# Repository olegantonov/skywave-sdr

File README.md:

# SkyWave SDR

**Transceptor modular open source com ESP32-S3, OLED, PTT e acesso USB.**
Projeto de Daniel Marques, com prioridade para baixo custo e montagem incremental.

A revisão **D1** inclui circuitos, oito projetos KiCad, seleção de componentes,
simulações, modelos STEP e gabinete paramétrico em STL. É um protótipo de engenharia:
nenhuma placa foi fabricada ou ensaiada fisicamente. O firmware disponível ainda é
de interface e mantém a transmissão bloqueada, pois drivers RF/DSP estão pendentes.

## Abrir o projeto

- **[Circuito, PCB, BOM, ligações e testes D1](hardware/d1/README.md)**
- [Esquemas e placas KiCad editáveis](hardware/d1/ecad)
- [PDFs dos esquemas e curvas dos filtros](hardware/d1/plots)
- [Montagem 3D STEP](hardware/d1/cad/skywave_d1_assembly.step)
- [Base STL](hardware/d1/cad/enclosure_base.stl) e [tampa STL](hardware/d1/cad/enclosure_lid.stl)
- [Relatórios ERC/DRC](hardware/d1/reports/checks.json), [simulações](hardware/d1/reports/simulation.json)
  e [geometria](hardware/d1/reports/mechanical.json)

## Arquitetura

| Bloco | Implementação D1 |
|---|---|
| Controle | ESP32-S3-WROOM-1-N8, OLED SH1106/SSD1306, botões e PTT físico |
| Acesso | USB-C de dados/console, GPIO19/20; alimentação externa regulada de 5 V |
| HF 40/20/15/10 m | Codec TLV320AIC3204, Si5351A, quadratura, misturadores I/Q RX/TX e filtros intercambiáveis |
| VHF 2 m | DRA818V, FM analógica controlada por UART, fonte e filtro próprios |
| UHF 70 cm | DRA818U, FM analógica controlada por UART, fonte e filtro próprios |
| Áudio | Eletreto externo, comutação analógica, LM386 e saída para falante de 8 Ω |
| Gabinete | Montagem de bancada 164 × 120 × 74 mm; miniaturização posterior |

**A versão econômica é híbrida.** HF tem arquitetura SDR I/Q; DRA818 VHF/UHF não
expõem amostras I/Q e não são SDR aberto. A expansão I/Q VHF/UHF continua planejada.
HF D1 é um excitador de baixo nível, sem PA. Nos DRA, H/L aterrado seleciona potência
nominal de 0,5 W; potência, sensibilidade e emissões não foram medidas neste projeto.

```mermaid
flowchart LR
    UI[OLED + botoes + PTT] <--> MCU[ESP32-S3]
    USB[USB-C dados] <--> MCU
    MCU <-->|I2S| CODEC[TLV320AIC3204]
    MCU -->|I2C| LO[Si5351 + quadratura]
    LO --> HF[Misturadores HF RX/TX]
    CODEC <--> HF
    HF <--> LPF[Rele T/R + cartucho LC]
    LPF <--> A[SMA HF]
    MIC[Microfone / falante] <--> AUDIO[Comutacao de audio]
    AUDIO <--> CODEC
    MCU -->|UART| V[DRA818V + filtro]
    MCU -->|UART| U[DRA818U + filtro]
    AUDIO <--> V
    AUDIO <--> U
    PWR[5 V externo] --> MCU
    PWR --> BUCK[Fontes RF 4 V]
    BUCK --> V
    BUCK --> U
```

O planejamento aproveitou a separação entre hardware, firmware, interface e energia
estudada no SkySentinel. Este repositório é independente: não publica código,
esquemas, memórias ou dados privados daquele projeto.

## Firmware

C++17 com Arduino/PlatformIO. Duas variantes OLED, sintonia por botões, console,
watchdog e lógica de PTT com timeout de 30 s. A frequência exibida é uma prévia;
a tela informa `PREVIEW - NO RF` e PTT resulta em `TX BLOQUEADO`.

Na D1, TX_ARM e PD dos módulos permanecem em zero, resets de codec/quadratura
ativos e seletor de módulo na posição desabilitada. Ainda faltam drivers do codec,
LO e DRA, DSP SSB, AGC, calibração I/Q e sequência de T/R com tempos medidos.

```bash
python3 -m venv .venv
. .venv/bin/activate
pip install platformio==6.1.18
pio run -e esp32s3_oled -e esp32s3_ssd1306
mkdir -p build
g++ -std=c++17 -Wall -Wextra -Werror -pedantic -fsanitize=undefined \
  -Ifirmware/include tests/radio_test.cpp -o build/radio_test
./build/radio_test
python3 tests/hardware_test.py
```

Console: `?` consulta estado, `+`/`-` sintonizam, `b` troca banda. Não existe
comando de transmissão remota. GPIOs estão em [`pins.h`](firmware/include/pins.h);
as ligações completas estão no [guia D1](hardware/d1/README.md).

## Validação e próximos passos

Os relatórios registram o que passou e os achados pendentes. Simulação ngspice,
ERC/DRC, testes de software e verificação de sólidos 3D não substituem ensaios de
bancada. PCB, stackup/impedâncias, dissipação, encaixes e acessórios precisam de
revisão antes da montagem; consultar o estado de fabricação nos relatórios D1.

A estratégia de custo é montar controle e apenas um módulo inicialmente. O preço
final ainda não foi cotado. A BOM identifica partes principais e especificações
de passivos; não é uma lista de compra fechada com frete e montagem.

Próximas etapas: validar fontes e interface, implementar HF RX, ensaiar HF TX em
carga de 50 Ω, integrar VHF/UHF FM e então desenvolver bateria e miniaturização.
Os perfis de frequência não são autorização para transmissão nem plano regulatório.

## Contribuição e licença

Contribuições por issues e PRs, com Conventional Commits e evidências de testes.
Arquivos originais: [MIT](LICENSE). Footprints KiCad mantêm sua
[licença própria](hardware/d1/ecad/SkyWave.pretty/LICENSE.md). Dependências,
datasheets e módulos comerciais mantêm as respectivas licenças.

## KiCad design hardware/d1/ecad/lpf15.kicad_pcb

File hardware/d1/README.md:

# SkyWave D1 — circuito, PCB e gabinete

Protótipo de engenharia de Daniel Marques. Os arquivos são editáveis; esta revisão
não é uma liberação para fabricação em série. Ensaios RF, térmicos e de montagem
física não foram realizados. O firmware continua sem backend RF e mantém TX bloqueado.

## Arquivos

- [Esquemas e placas KiCad](ecad): oito projetos, biblioteca local e roteamento.
- [BOM por referência](bom.csv) e [circuito com todas as conexões](design.json).
- [Fontes dos fabricantes](sources.json), com hashes quando o PDF foi obtido.
- [Montagem STEP](cad/skywave_d1_assembly.step), placas individuais, base e tampa em STEP/STL.
- [Simulações](reports/simulation.json), [ERC/DRC completos](reports/checks.json)
  e [verificação mecânica](reports/mechanical.json).
- [Curvas dos filtros](plots/filter_response.pdf) e [netlists ngspice](simulation).
- [Gerber e Excellon por placa](fabrication_prototype), exportados com o bloqueio de verificações ativo.

## Resultado das verificações — 12/10/2026

| Verificação executada | Resultado |
|---|---|
| KiCad ERC/DRC, 8 placas | Zero erros, zero avisos e zero conexões pendentes |
| 915 pads comparados ao circuito | Redes, números de pino, valores e posições conferem |
| 6 filtros em ngspice | Conferem com cálculo independente por matrizes ABCD |
| 1.800 casos de tolerância LC | Atendem às metas do modelo com Q=35; não são medições |
| Modelos STEP e interseções | Sólidos válidos, sem colisões entre placas ou contra base/tampa |
| Firmware | Duas variantes compiladas; testes nativos de controle passaram com UBSan |
| Contratos de artefatos | 4 testes Python passaram |

Hashes das placas e esquemas constam dos relatórios. Os testes digitais de PTT e
quadratura são verificações lógicas; não incluem atrasos reais dos componentes.
O resultado não valida o desempenho do rádio completo nem substitui bancada.

## Placas e componentes

| Placa | Dimensões | Circuito |
|---|---|---|
| Controle | 120 × 100 mm, 2 camadas | ESP32-S3-WROOM-1-N8, OLED I²C externo, USB4105, USBLC6-2SC6, LM1117, lógica de PTT, CD74HCT4052, LM386 |
| HF | 120 × 100 mm, 4 camadas | TLV320AIC3204, TLV75518, Si5351A, 74LVC74A, dois SN74CBT3253, dois TLV9064, relé G6K |
| VHF | 60 × 70 mm, 4 camadas | DRA818V, TPS62160, buffer UART e filtro de saída |
| UHF | 60 × 70 mm, 4 camadas | DRA818U, TPS62160, buffer UART e filtro de saída |
| Filtros HF | 48 × 24 mm cada, 4 camadas | Cartuchos LC de sete polos para 40/20/15/10 m, identificação resistiva |

HF usa conversão I/Q em recepção e transmissão. É um **excitador de baixo nível**,
sem PA. A potência e a supressão de imagem/portadora ainda precisam ser medidas.
Os DRA818 são módulos de voz FM controlados por UART; **não oferecem SDR I/Q aberto**.
H/L aterrado seleciona o modo nominal de 0,5 W, que não foi medido neste projeto.
Somente um módulo pode receber habilitação de transmissão por vez.

A BOM contém MPNs dos circuitos principais e famílias/especificações de parte dos
passivos. Ainda requer fechamento dos códigos de compra, preços e equivalentes.
Os indutores HF são Coilcraft 0805CS; a simulação com Q=35 não garante o Q real
desses componentes em cada frequência. Confirmar perdas e autorressonância na bancada.
O relatório também calcula a sensibilidade a Q=10/20/35/50. O indutor de potência
TDK VLS3015ET-2R2M está marcado NRND pelo fabricante; para a próxima revisão,
selecionar uma alternativa ativa e conferir novamente footprint, corrente e perdas.

## Energia, portas e conexões

**Entrada: 5 V regulados, fonte de pelo menos 2 A em J3 da placa de controle.**
J3.1 = +5 V; J3.2 = GND. Não há proteção contra inversão, carregador, bateria ou
power-path. USB-C nesta revisão leva **dados e referência VBUS para ESD**; não
alimenta o sistema. Nunca ligar célula de lítio diretamente a J3.

O LM1117 fornece 3,3 V. A dissipação estimada a 400 mA é 0,68 W; temperatura precisa
ser medida. Cada DRA tem buck de aproximadamente 4,02 V, nominalmente até 1 A.
O cálculo de consumo está em `reports/simulation.json`; não é autonomia medida.

| Interface do controle | Ligação |
|---|---|
| J1 PTT externo | 1 = PTT ativo em zero; 2 = GND; contato normalmente aberto |
| J2 OLED | 1 GND, 2 +3V3, 3 SCL, 4 SDA; verificar ordem no módulo comprado |
| J3 energia | 1 +5V, 2 GND |
| J4 USB-C | Console e programação; GPIO19 D− / GPIO20 D+ |
| J5 HF, 2×10 | Cabo pino a pino para J1 HF; máximo curto de bancada, ainda sem SI medida |
| J6 VHF / J7 UHF, 2×5 | Cabo pino a pino para J1 do módulo correspondente |
| J8 microfone | 1 sinal polarizado, 2 GND; cápsula eletreto externa |
| J9 alto-falante | 1 áudio desacoplado, 2 GND; 8 Ω |

As tabelas completas de pinos e redes estão em `design.json` e nos esquemas.
Orientar os cabos pelo pino 1, não pela posição visual dos conectores.
Os cartuchos HF usam cabo curto 2×3 para J2 HF; instalar somente um cartucho por vez.
Usam IDs de 1 kΩ, 2,2 kΩ, 4,7 kΩ e 10 kΩ. A leitura/validação pelo firmware está pendente.

PTT físico e GPIO38/TX_ARM passam por lógica AND/NAND e decodificador SN74HC139.
GPIO39/40 selecionam HF/VHF/UHF; valor 3 desabilita todos. GPIO41/42 controlam PD
dos DRA. Pull-down em TX_ARM mantém TX desabilitado durante reset; o firmware
mantém ARM, PD, reset do codec e reset da quadratura em zero nesta revisão.
Essa lógica não mede filtro, potência, VSWR ou temperatura.

## Limites do layout e da mecânica

O roteamento é um ponto de partida para revisão elétrica. ERC/DRC verificam regras
geométricas e conectividade; não demonstram integridade de sinal, impedância RF,
estabilidade do buck, USB ou desempenho do codec. Conferir os relatórios completos,
incluindo ligações pendentes e avisos, antes de qualquer pedido de placas.
O stackup precisa ser acordado com o fabricante; linhas RF de 50 Ω, par USB de
90 Ω, retorno de terra e desacoplamentos exigem revisão específica.

O gabinete de bancada mede **164 × 120 × 74 mm**, com paredes de 2,5 mm. É uma
primeira montagem modular, maior que o formato portátil final. As placas recebem
suportes internos; a tampa tem janela de display, três botões e ventilação.
Há acesso ao USB e passagens para PTT, energia e três SMA de painel com pigtails.
Conectores, speaker, microfone e cabos de painel ainda não têm montagem física validada.

Os STEP dos componentes usam envelopes derivados de footprints, não modelos
certificados de fabricante. A bandeja OLED assume módulo de 35,6 × 33,7 mm;
medir o módulo escolhido e ajustar `mechanical.py` antes de imprimir. Folgas de
impressão, curso dos botões, parafusos e volume de cabos precisam de ensaio.

## Reprodução

Os scripts originais estão em [`tools/hardware`](../../tools/hardware).
Dependências utilizadas: KiCad 7 para `pcbnew`, KiCad CLI 10.0.7 para ERC/DRC,
CadQuery 2.8.0, NumPy, Matplotlib, sexpdata, ngspice 42 e Freerouting 2.1.0/Java 21.
Os caminhos de ferramentas podem ser configurados por variáveis de ambiente;
os defaults refletem a estação de desenvolvimento.

1. `python tools/hardware/acquire.py`: obter referências públicas.
2. `python tools/hardware/ecad.py`: gerar esquemas e placas iniciais. **Sobrescreve roteamento.**
3. `python tools/hardware/route.py prepare`: preparar DSNs; executar Freerouting
   em cada DSN e salvar SES com o mesmo nome.
   Para HF, executar `hf_escape.py` antes do roteador: ele prepara escapes alternados
   dos encapsulamentos finos com vias de 0,5/0,25 mm.
4. `python tools/hardware/route.py finish`: importar trilhas/vias e preencher planos.
   Aplicar `refine.py` em HF/VHF/UHF para acabamento dos SMA, PTT e costura de terra.
5. `python tools/hardware/check.py`: executar ERC/DRC reais, sem apagar achados.
   `verify_pcb.py` confere os pads dos arquivos salvos contra o circuito.
   `cleanup.py <placas>` remove apenas stubs apontados pelo DRC; repetir a verificação
   após essa edição. Mudanças nas placas invalidam os hashes anteriores.
6. `python tools/hardware/analyze.py`: executar ngspice e tolerâncias dos filtros.
7. `python tools/hardware/mechanical.py` e `render.py`: gerar STEP/STL e imagem.

`export.py --manufacturing` só exporta Gerber/Excellon quando ERC/conectividade/DRC
passaram e o hash da placa confere com o relatório. A exportação continua marcada
como protótipo. Há uma regra explícita para os pads SMA de montagem na borda;
as demais regiões mantêm afastamento de 0,5 mm da borda. Vias em pads exigem
avaliação de montagem; esta revisão prioriza soldagem e inspeção de bancada.

Não foram fabricadas, energizadas ou testadas placas físicas durante esta revisão.
Próximos ensaios: fontes sem RF, OLED/USB/PTT, clock e codec, RX, depois TX em carga
de 50 Ω com analisador de espectro. Firmware DSP, drivers e sequência de T/R pendentes.

## Licenças

Arquivos originais: [MIT](../../LICENSE). Footprints copiados da biblioteca KiCad 7
mantêm [CC-BY-SA 4.0 com exceção KiCad](ecad/SkyWave.pretty/LICENSE.md); origem:
https://github.com/KiCad/kicad-footprints. A biblioteca foi copiada para tornar os
projetos independentes da versão instalada. DRA818 e VLS3015ET são footprints
originais deste projeto. Datasheets não são redistribuídos sob MIT.
O footprint MSOP-10 foi adaptado para herdar a regra de espaçamento de 0,15 mm
do projeto, em vez de impor o override de 0,20 mm da biblioteca original.

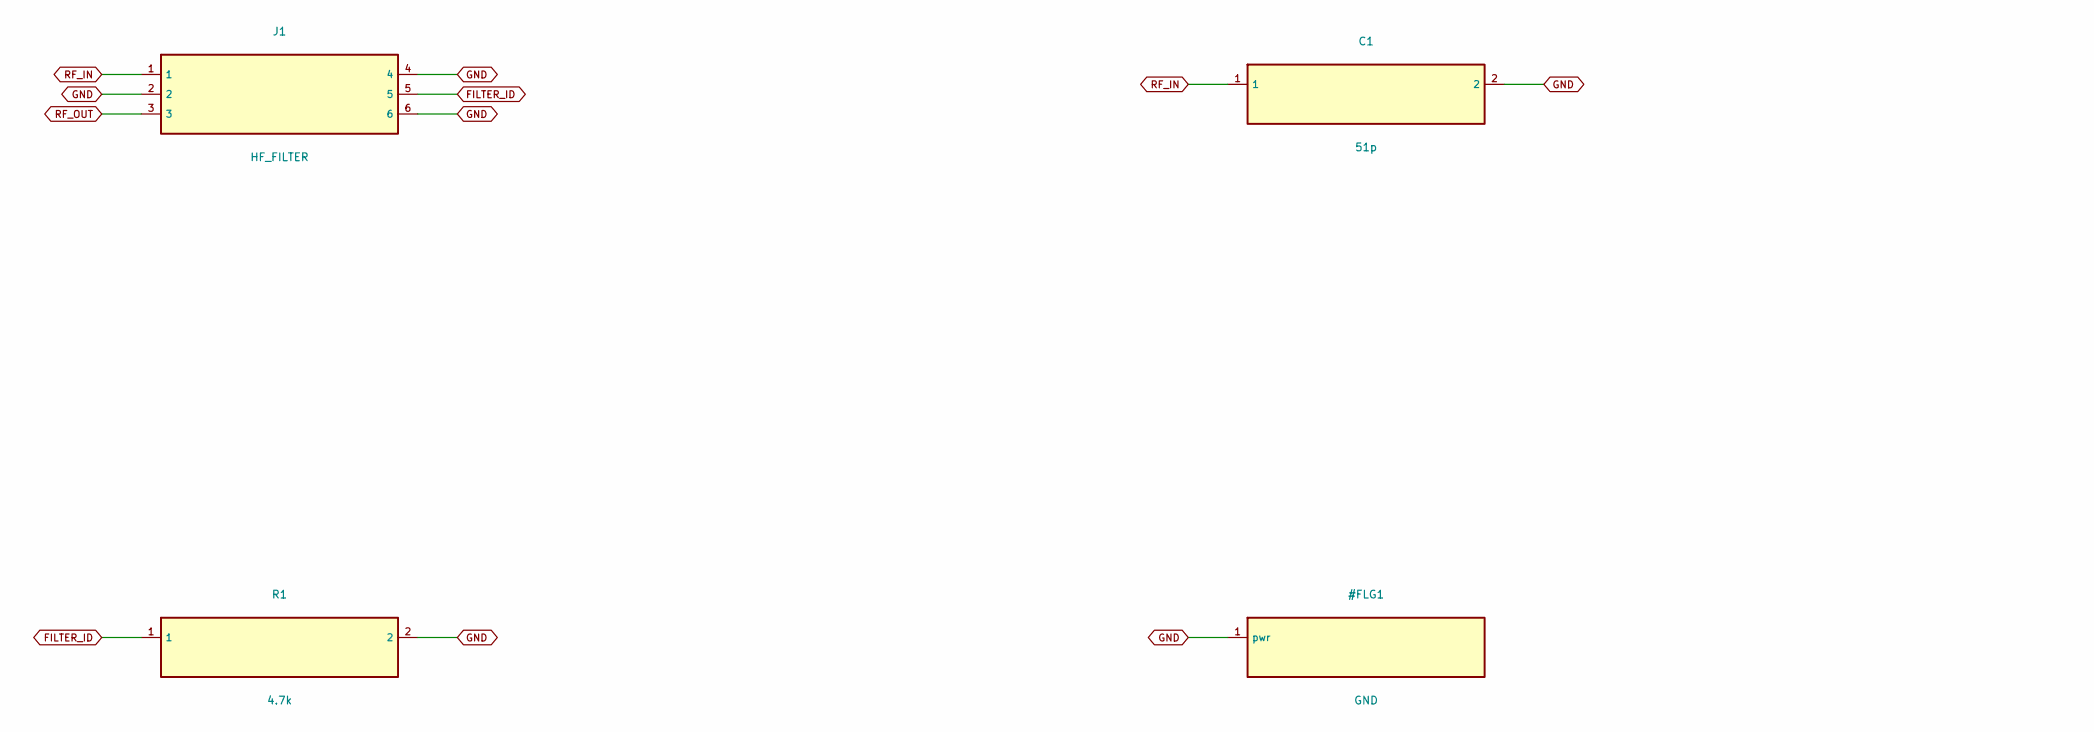
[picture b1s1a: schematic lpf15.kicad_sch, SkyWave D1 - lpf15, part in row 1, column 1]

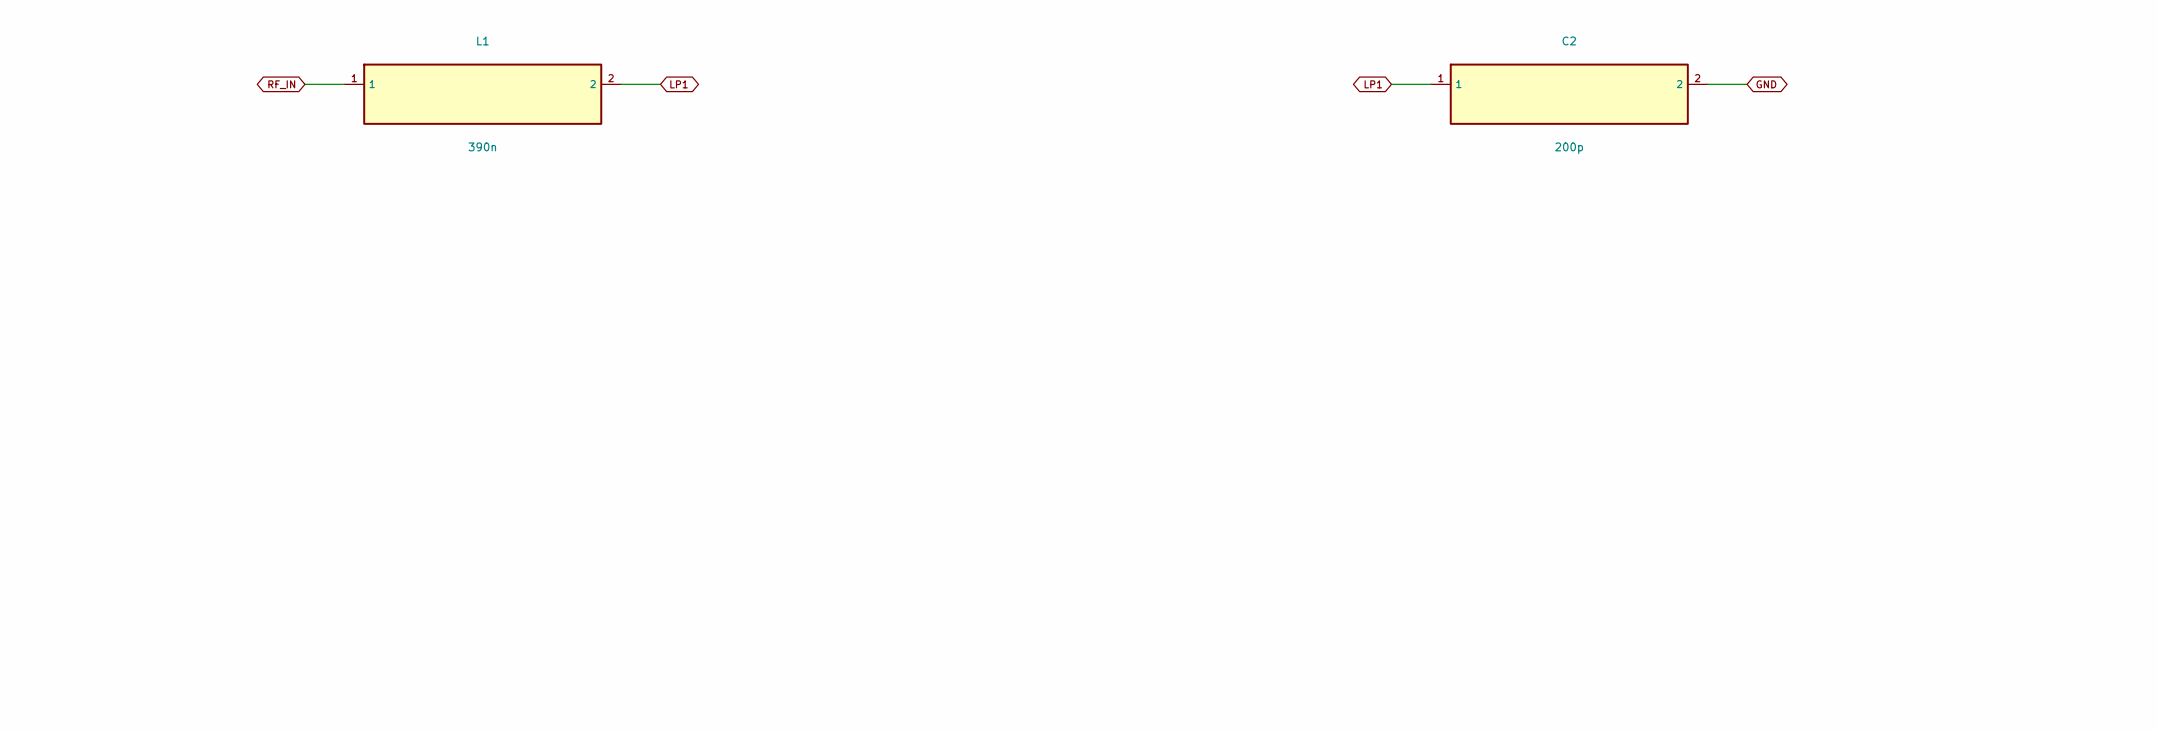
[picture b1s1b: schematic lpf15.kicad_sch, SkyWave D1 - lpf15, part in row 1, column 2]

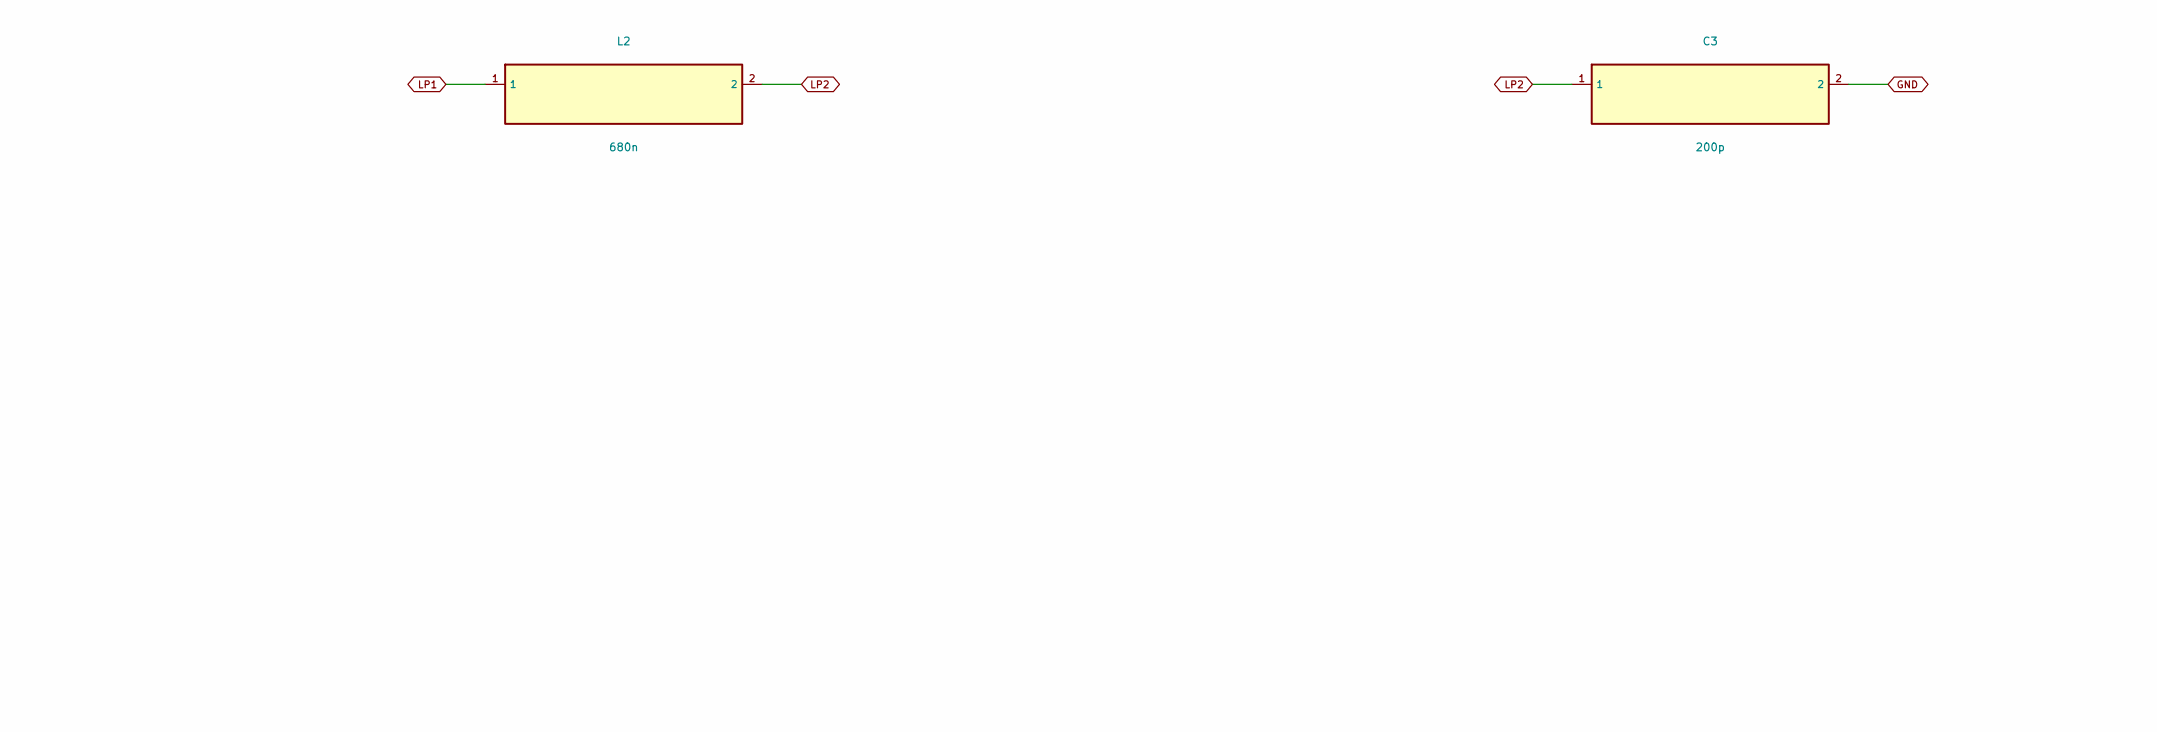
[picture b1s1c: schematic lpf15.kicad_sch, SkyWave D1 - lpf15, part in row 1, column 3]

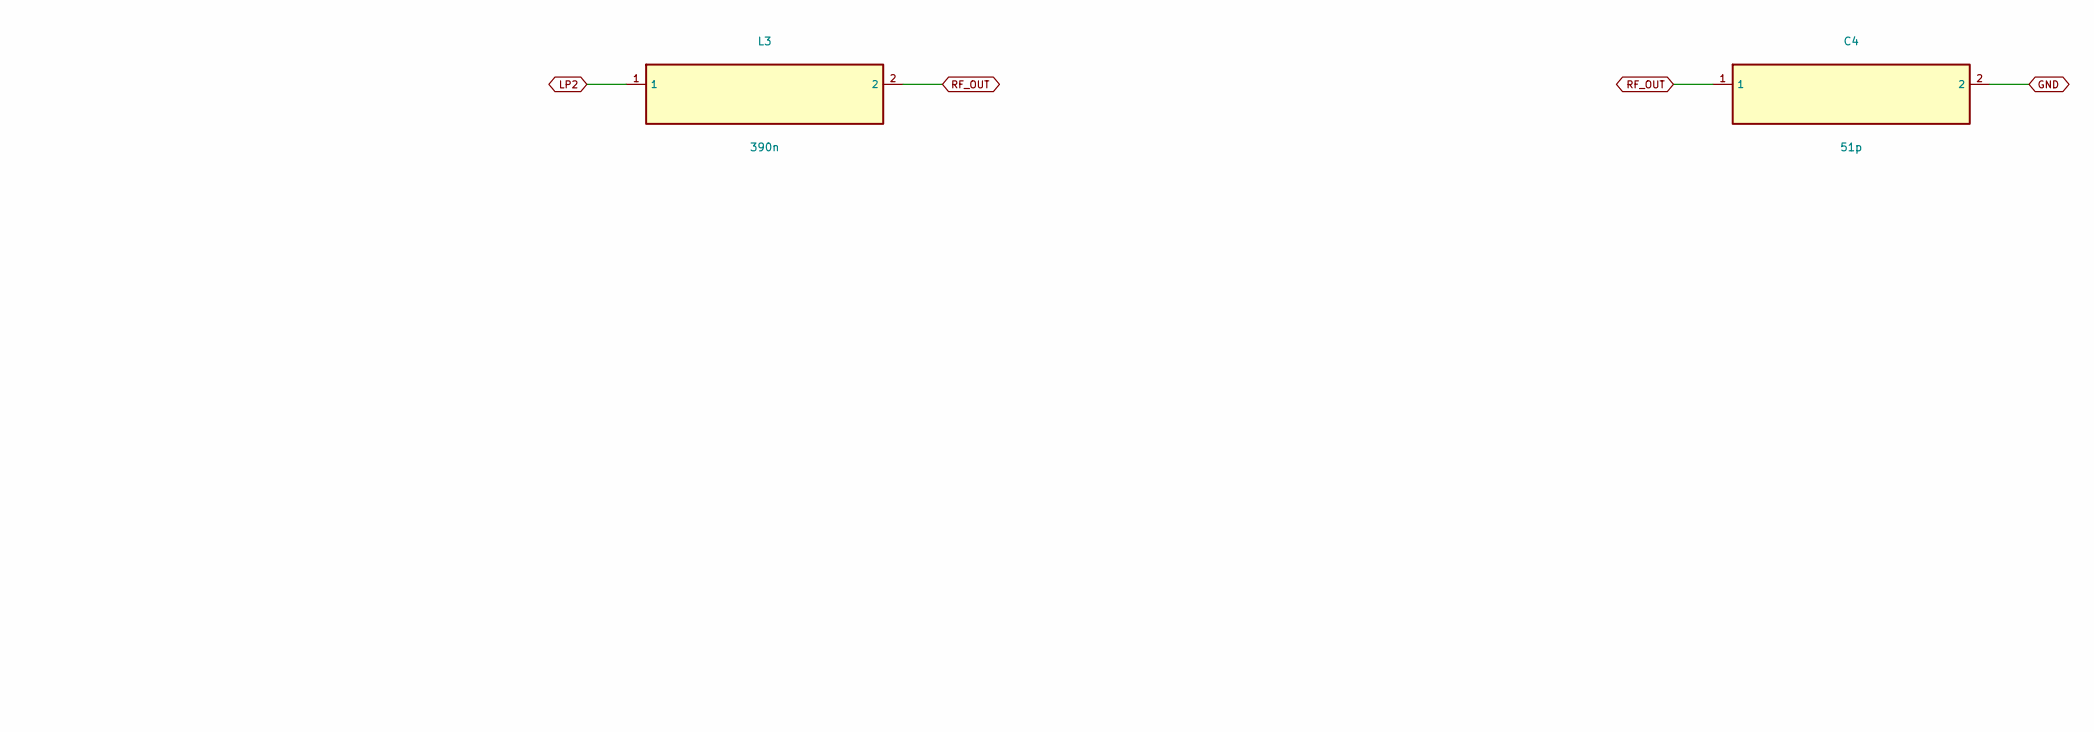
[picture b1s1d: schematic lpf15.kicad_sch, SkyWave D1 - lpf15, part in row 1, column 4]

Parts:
C1, C4: 51p; Capacitor_SMD_C_0603_1608Metric; MPN KEMET 0603 C0G 25V; 51p; 5% RF/10% deco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
C2, C3: 200p; Capacitor_SMD_C_0603_1608Metric; MPN KEMET 0603 C0G 25V; 200p; 5% RF/10% dec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
J1: HF_FILTER; Connector_PinHeader_2.54mm_PinHeader_2x03_P2.54mm_Vertical; MPN Samtec TSW-003-07-D-S
L1, L3: 390n; Inductor_SMD_L_0805_2012Metric; MPN 0805CS-391XJRC
L2: 680n; Inductor_SMD_L_0805_2012Metric; MPN 0805CS-681XJRC
R1: 4.7k; Resistor_SMD_R_0603_1608Metric; MPN CRCW0603 series; value=4.7k; 1%

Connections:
FILTER_ID: J1.5, R1.1
GND: C1.2, C2.2, C3.2, C4.2, J1.2, J1.4, J1.6, R1.2
LP1: C2.1, L1.2, L2.1
LP2: C3.1, L2.2, L3.1
RF_IN: C1.1, J1.1, L1.1
RF_OUT: C4.1, J1.3, L3.2

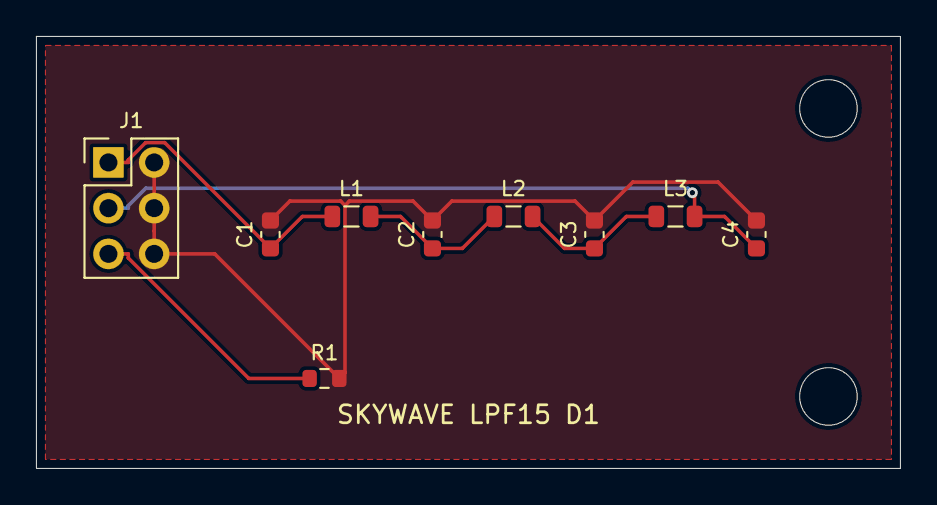
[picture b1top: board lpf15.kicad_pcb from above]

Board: 4 copper layers, 48.0 x 24.0 mm, 11 parts (0 on the bottom side), 6 nets.

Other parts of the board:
H1, H2: MountingHole_3.2mm_M3

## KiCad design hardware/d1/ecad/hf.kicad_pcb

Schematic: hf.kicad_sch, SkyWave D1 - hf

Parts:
C1, C2, C8, C9, C16, C20, C22, C25: 1u; Capacitor_SMD_C_0603_1608Metric; MPN KEMET 0603 X7R 25V; 1u; 5% RF/10% decou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
C3, C4, C5, C6, C10, C11, C21, C28, C29, C30, C35, C36: 100n; Capacitor_SMD_C_0603_1608Metric; MPN KEMET 0603 X7R 25V; 100n; 5% RF/10% dec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
C7, C12, C37, C38: 10u; Capacitor_SMD_C_0805_2012Metric; MPN KEMET 0805 X7R 25V; 10u; 5% RF/10% deco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
C13, C14, C17, C18: 100p; Capacitor_SMD_C_0603_1608Metric; MPN KEMET 0603 C0G 25V; 100p; 5% RF/10% dec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
C15, C19, C23, C24, C26, C27, C31, C32, C33, C34: 10n; Capacitor_SMD_C_0603_1608Metric; MPN KEMET 0603 C0G 25V; 10n; 5% RF/10% deco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
D1: 1N4148W; Diode_SMD_D_SOD-123; MPN 1N4148W
J1: CONTROL_INTERFACE; Connector_PinHeader_2.54mm_PinHeader_2x10_P2.54mm_Vertical; MPN Samtec TSW-010-07-D-S
J2: FILTER_CARTRIDGE; Connector_PinHeader_2.54mm_PinHeader_2x03_P2.54mm_Vertical; MPN Samtec TSW-003-07-D-S
J3: SMA 132289; Connector_Coaxial_SMA_Amphenol_132289_EdgeMount; MPN Amphenol 132289
K1: G6K-2F-Y-DC5; Relay_SMD_Relay_DPDT_Omron_G6K-2F-Y; MPN G6K-2F-Y-DC5
Q1: 2N7002; Package_TO_SOT_SMD_SOT-23; MPN 2N7002
R1, R3, R4, R5, R6, R7, R9, R12, R14, R18, R19, R23, R24: 10k; Resistor_SMD_R_0603_1608Metric; MPN CRCW0603 series; value=10k; 1%
R2: 33; Resistor_SMD_R_0603_1608Metric; MPN CRCW0603 series; value=33; 1%
R8, R10, R13, R15, R17, R22, R29: 100k; Resistor_SMD_R_0603_1608Metric; MPN CRCW0603 series; value=100k; 1%
R11, R16: 1k; Resistor_SMD_R_0603_1608Metric; MPN CRCW0603 series; value=1k; 1%
R20, R21, R25, R26: 100; Resistor_SMD_R_0603_1608Metric; MPN CRCW0603 series; value=100; 1%
R27, R28: 49.9; Resistor_SMD_R_0603_1608Metric; MPN CRCW0603 series; value=49.9; 1%
U1: TLV75518PDBVR; Package_TO_SOT_SMD_SOT-23-5; MPN TLV75518PDBVR
U2: TLV320AIC3204IRHBR; Package_DFN_QFN_Texas_RHB0032E_VQFN-32-1EP_5x5mm_P0.5mm_EP3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; MPN TLV320AIC3204IRHBR
U3: SI5351A-B-GT; Package_SO_MSOP-10_3x3mm_P0.5mm; MPN SI5351A-B-GT
U4: 74LVC74APW; Package_SO_TSSOP-14_4.4x5mm_P0.65mm; MPN 74LVC74APW
U5: SN74LVC1G04DBVR; Package_TO_SOT_SMD_SOT-23-5; MPN SN74LVC1G04DBVR
U6, U7: TLV9064IDR; Package_SO_SOIC-14_3.9x8.7mm_P1.27mm; MPN TLV9064IDR
U8, U9: SN74CBT3253DR; Package_SO_SOIC-16_3.9x9.9mm_P1.27mm; MPN SN74CBT3253DR
Y1: 25MHz 10pF; Crystal_Crystal_SMD_3225-4Pin_3.2x2.5mm; MPN Abracon ABM8-25.000MHZ-10-1-U-T

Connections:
+1V8: C2.1, C4.1, C5.1, U1.5 (OUT), U2.24 (AVDD), U2.29 (DVDD)
+3V3: C1.1, C3.1, C6.1, C10.1, C11.1, C38.1, J1.3, R4.2, U1.1, U1.3, U2.6 (IOVDD), U2.26 (LDOIN), U3.1, U3.7, U4.4, U4.10, U4.14, U5.5
+5V: C21.1, C28.1, C29.1, C30.1, C37.1, D1.1, J1.1, K1.1, R5.1, U6.4, U7.4, U8.16, U9.16
ADC_I: C16.2, U2.13 (IN1L)
ADC_Q: C20.2, U2.14 (IN1R)
ANT_HF: J2.3, J3.1
AUDIO_RAW: C8.1, U2.25 (HPL)
CODEC_REF: C7.1, U2.18 (REF)
CODEC_RESET_N: J1.12, R1.1, U2.31 (RESET)
COIL_LOW: D1.2, K1.8, Q1.3
DAC_I: C22.1, U2.22 (LOL)
DAC_Q: C25.1, U2.23 (LOR)
DET_IN: C34.1, R9.1, U8.3, U8.13
DET_IP: C31.1, R7.1, U8.6, U8.10
DET_QN: C33.1, R14.1, U8.4, U8.12
DET_QP: C32.1, R12.1, U8.5, U8.11
FILTER_ID: J1.17, J2.5
GND: C1.2, C2.2, C3.2, C4.2, C5.2, C6.2, C7.2, C10.2, C11.2, C12.2, C15.2, C19.2, C21.2, C28.2, C29.2, C30.2, C37.2, C38.2, J1.2, J1.4, J1.16, J1.19, J1.20, J2.2, J2.4, J2.6, J3.2, Q1.2, R1.2, R3.2, R6.2, R29.2, U1.2, U2.7 (IOVSS), U2.8 (MFP3), U2.12 (SPI_SEL), U2.17 (AVSS), U2.28 (DVSS), U2.30 (LDO_SEL), U2.33 (EP), U3.8, U4.7, U5.3, U6.11, U7.11, U8.8, U9.8, Y1.2, Y1.4
HF_AUDIO: C8.2, J1.14
HF_MIC: C9.1, J1.15
HF_TX: Q1.1, R29.1, U5.4 (Y), U8.1, U8.15
HF_TX_N: J1.13, R4.1, U5.2, U9.1, U9.15
I2C_SCL: J1.6, U2.9 (SCL), U3.4 (SCL)
I2C_SDA: J1.5, U2.10 (SDA), U3.5 (SDA)
I2S_BCLK: J1.8, U2.2 (BCLK)
I2S_LRCK: J1.9, U2.3 (WCLK)
I2S_MCLK: J1.7, U2.1 (MCLK)
I2S_RX: J1.11, U2.5 (DOUT)
I2S_TX: J1.10, U2.4 (DIN)
LO4: R2.2, U4.3, U4.11
LO4_RAW: R2.1, U3.10 (CLK0)
LO_I: U4.5 (1Q), U4.12, U8.14, U9.14
LO_Q: U4.9 (2Q), U8.2, U9.2
LO_Q_N: U4.2, U4.8 (2Q_N)
LO_RESET_N: J1.18, R3.1, U4.1, U4.13
LP_I: C15.1, C16.1, R11.2
LP_Q: C19.1, C20.1, R16.2
MIC_IN: C9.2, U2.15 (IN2L)
MIX_RX: C35.2, R27.1, U8.7, U8.9
MIX_TX: C36.1, U9.7, U9.9
RF_COMMON: J2.1, K1.3
RF_RX: C35.1, K1.2
RF_TX: K1.4, R28.2
RX_I: C14.2, R10.2, R11.1, U6.1 (OUT1)
RX_I_NEG: C14.1, R9.2, R10.1, U6.2
RX_I_POS: C13.1, R7.2, R8.1, U6.3
RX_Q: C18.2, R15.2, R16.1, U6.7 (OUT2)
RX_Q_NEG: C18.1, R14.2, R15.1, U6.6
RX_Q_POS: C17.1, R12.2, R13.1, U6.5
SPARE_OUT: U6.13, U6.14 (OUT4)
TX_AC: C36.2, R28.1
TX_IN: R19.2, R21.1, U7.7 (OUT2)
TX_IN_F: C24.1, R21.2, U9.3, U9.13
TX_IP: R18.1, R20.1, U7.1 (OUT1), U7.2
TX_IP_F: C23.1, R20.2, U9.6, U9.10
TX_I_BIAS: C22.2, R17.1, U7.3
TX_I_INV: R18.2, R19.1, U7.6
TX_QN: R24.2, R26.1, U7.14 (OUT4)
TX_QN_F: C27.1, R26.2, U9.4, U9.12
TX_QP: R23.1, R25.1, U7.8 (OUT3), U7.9
TX_QP_F: C26.1, R25.2, U9.5, U9.11
TX_Q_BIAS: C25.2, R22.1, U7.10
TX_Q_INV: R23.2, R24.1, U7.13
VMID: C13.2, C17.2, C23.2, C24.2, C26.2, C27.2, C31.2, C32.2, C33.2, C34.2, R8.2, R13.2, R17.2, R22.2, R27.2, U6.8 (OUT3), U6.9, U6.12, U7.5, U7.12
VMID_RAW: C12.1, R5.2, R6.1, U6.10
XTAL_A: U3.2, Y1.1
XTAL_B: U3.3, Y1.3

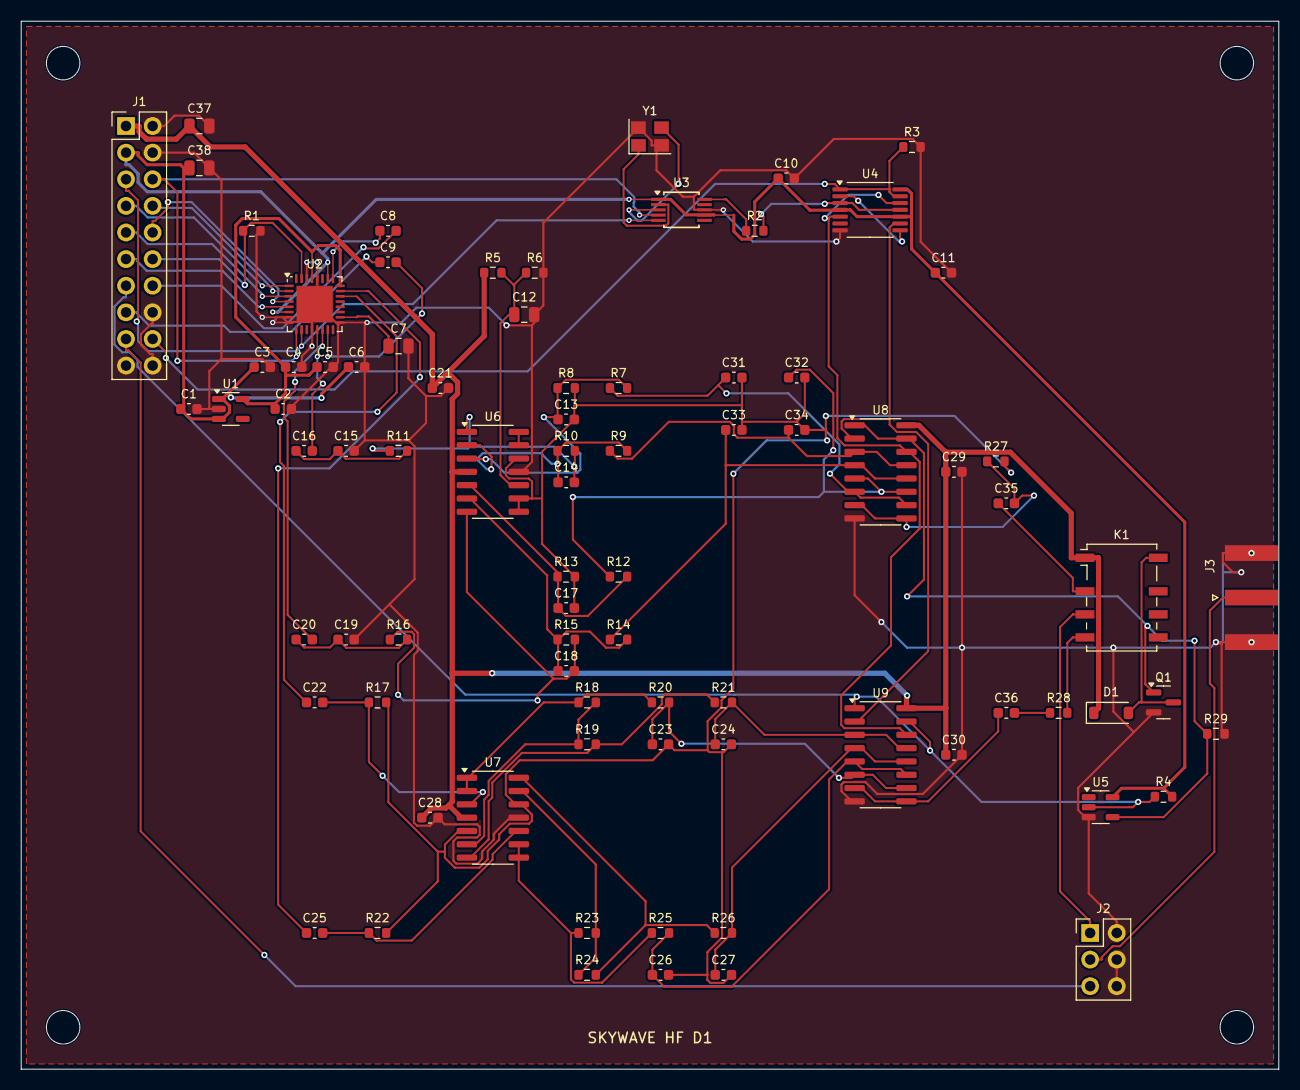
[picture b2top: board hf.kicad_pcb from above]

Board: 4 copper layers, 120.0 x 100.0 mm, 87 parts (0 on the bottom side), 67 nets.

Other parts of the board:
H1, H2, H3, H4: MountingHole_3.2mm_M3

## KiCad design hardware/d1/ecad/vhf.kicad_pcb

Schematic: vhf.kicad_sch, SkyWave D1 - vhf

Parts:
C1: 10u; Capacitor_SMD_C_0805_2012Metric; MPN KEMET 0805 X7R 25V; 10u; 5% RF/10% deco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
C2, C4: 22u; Capacitor_SMD_C_0805_2012Metric; MPN KEMET 0805 X7R 25V; 22u; 5% RF/10% deco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
C3, C5, C6: 100n; Capacitor_SMD_C_0603_1608Metric; MPN KEMET 0603 X7R 25V; 100n; 5% RF/10% dec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
C7, C8: 1u; Capacitor_SMD_C_0603_1608Metric; MPN KEMET 0603 X7R 25V; 1u; 5% RF/10% decou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
C9, C12: 7.5p; Capacitor_SMD_C_0603_1608Metric; MPN KEMET 0603 C0G 25V; 7.5p; 5% RF/10% dec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
C10, C11: 30p; Capacitor_SMD_C_0603_1608Metric; MPN KEMET 0603 C0G 25V; 30p; 5% RF/10% deco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
J1: CONTROL_INTERFACE; Connector_PinHeader_2.54mm_PinHeader_2x05_P2.54mm_Vertical; MPN Samtec TSW-005-07-D-S
J2: SMA 132289; Connector_Coaxial_SMA_Amphenol_132289_EdgeMount; MPN Amphenol 132289
L1: 2.2u; VLS3015ET; MPN VLS3015ET-2R2M
L2, L4: 47n; Inductor_SMD_L_0805_2012Metric; MPN 0805CS-470XJRC
L3: 82n; Inductor_SMD_L_0805_2012Metric; MPN 0805CS-820XJRC
Q1: 2N7002; Package_TO_SOT_SMD_SOT-23; MPN 2N7002
R1: 402k; Resistor_SMD_R_0603_1608Metric; MPN CRCW0603 series; value=402k; 1%
R2, R5, R6: 100k; Resistor_SMD_R_0603_1608Metric; MPN CRCW0603 series; value=100k; 1%
R3: 1k; Resistor_SMD_R_0603_1608Metric; MPN CRCW0603 series; value=1k; 1%
R4, R7: 10k; Resistor_SMD_R_0603_1608Metric; MPN CRCW0603 series; value=10k; 1%
U1: DRA818V; DRA818; MPN DRA818V
U2: TPS62160DGKR; Package_SO_VSSOP-8_3.0x3.0mm_P0.65mm; MPN TPS62160DGKR
U3: SN74LVC1G17DBVR; Package_TO_SOT_SMD_SOT-23-5; MPN SN74LVC1G17DBVR
U4: SN74LVC1G04DBVR; Package_TO_SOT_SMD_SOT-23-5; MPN SN74LVC1G04DBVR

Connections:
+3V3: C5.1, C6.1, J1.10, R7.2, U3.5, U4.5
+4V: C2.1, C3.1, C4.1, L1.2, R1.1, R4.2, U1.8 (VBAT), U2.6
+5V: C1.1, J1.1, U2.2, U2.3
AUDIO: C8.2, J1.8
AUDIO_RAW: C8.1, U1.3 (AF_OUT)
BUCK_FB: R1.2, R2.1, U2.5
BUCK_SW: L1.1, U2.7 (SW)
DRA_PTT_N: Q1.3, R4.1, U1.5 (PTT)
GND: C1.2, C2.2, C3.2, C4.2, C5.2, C6.2, C9.2, C10.2, C11.2, C12.2, J1.2, J1.9, J2.2, Q1.2, R2.2, R5.2, R6.2, U1.7, U1.9, U1.10, U2.1, U2.4, U3.3, U4.3
LP1: C10.1, L2.2, L3.1
LP2: C11.1, L3.2, L4.1
MIC: C7.1, J1.7
MIC_IN: C7.2, U1.18
PD: J1.6, R6.1, U1.6 (PD)
PTT_GATE: Q1.1, R5.1, U4.4 (Y)
PTT_N: J1.5, R7.1, U4.2
RF_FILTERED: C12.1, J2.1, L4.2
RF_RAW: C9.1, L2.1, U1.12
UART_IN: J1.3, R3.1
UART_IN_R: R3.2, U1.16 (RXD)
UART_OUT: J1.4, U3.4 (Y)
UART_OUT_RAW: U1.17 (TXD), U3.2

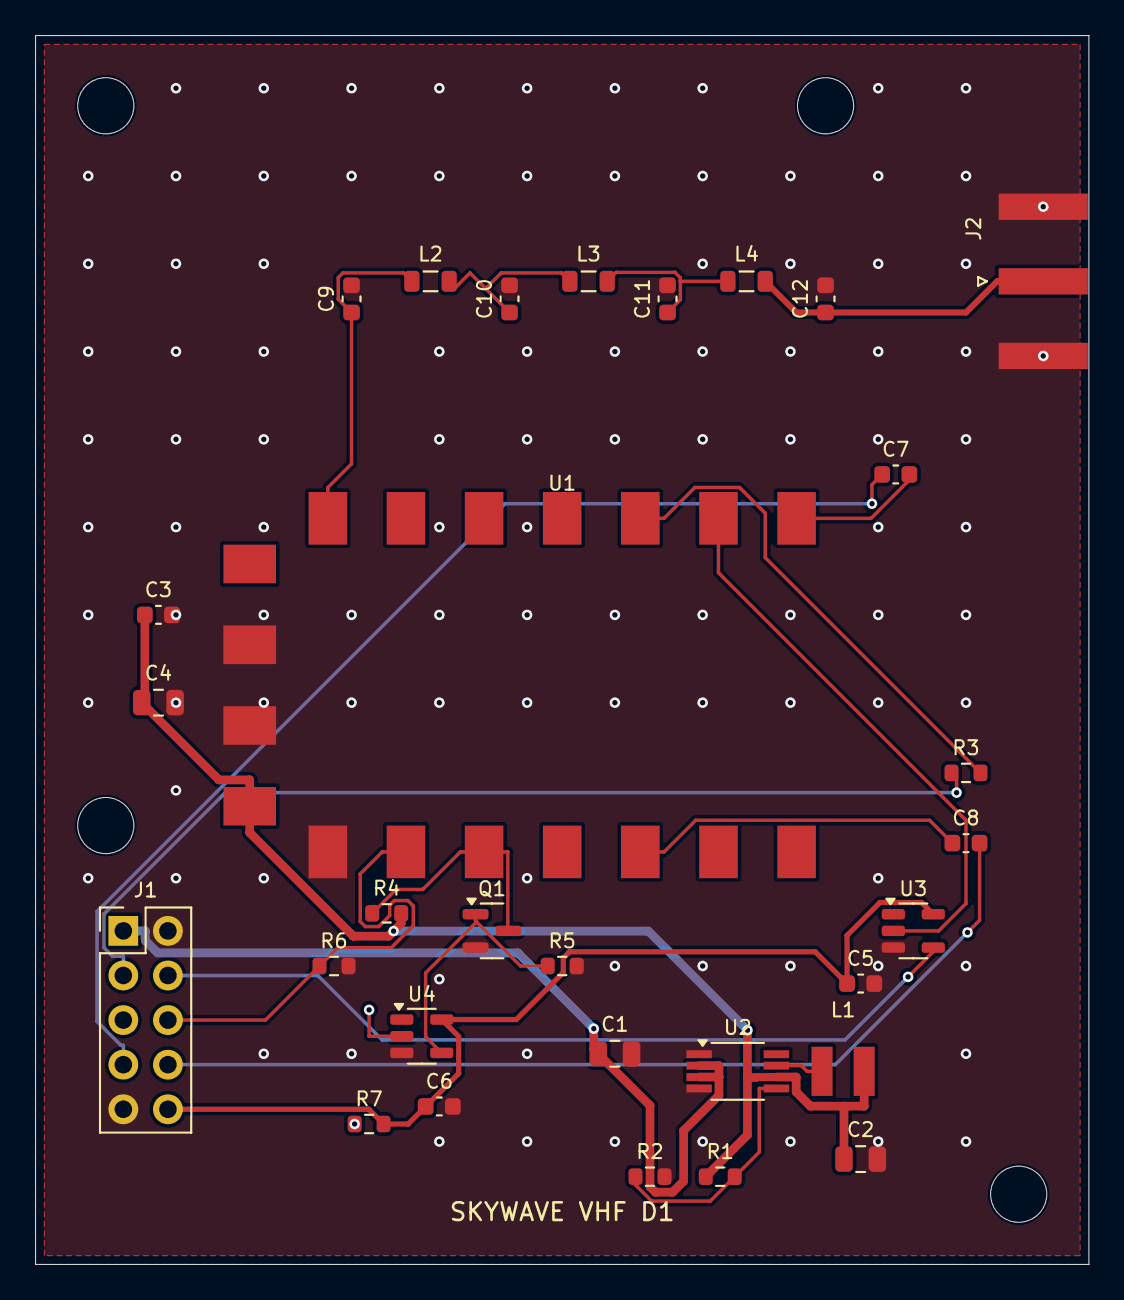
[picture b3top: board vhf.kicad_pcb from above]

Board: 4 copper layers, 60.0 x 70.0 mm, 34 parts (0 on the bottom side), 22 nets.

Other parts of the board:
H1, H2, H3, H4: MountingHole_3.2mm_M3

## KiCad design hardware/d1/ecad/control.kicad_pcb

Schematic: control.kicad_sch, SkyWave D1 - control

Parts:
C1, C10, C11, C12, C13, C14, C15, C16, C17: 1u; Capacitor_SMD_C_0603_1608Metric; MPN KEMET 0603 X7R 25V; 1u; 5% RF/10% decou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
C2, C4, C7, C8, C19, C20, C22, C23, C24, C25: 100n; Capacitor_SMD_C_0603_1608Metric; MPN KEMET 0603 X7R 25V; 100n; 5% RF/10% dec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
C3, C6, C9, C18: 10u; Capacitor_SMD_C_0805_2012Metric; MPN KEMET 0805 X7R 25V; 10u; 5% RF/10% deco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
C5: 22u tantalum; Capacitor_Tantalum_SMD_CP_EIA-3528-21_Kemet-B; MPN T491B226K016AT
C21: 220u; Capacitor_THT_CP_Radial_D6.3mm_P2.50mm; MPN EEUFR1A221
J1: PTT_PANEL; Connector_PinHeader_2.54mm_PinHeader_1x02_P2.54mm_Vertical; MPN Samtec TSW-002-07-S-S
J2: OLED_I2C; Connector_PinHeader_2.54mm_PinHeader_1x04_P2.54mm_Vertical; MPN Samtec TSW-004-07-S-S
J3: POWER_5V; Connector_PinHeader_2.54mm_PinHeader_1x02_P2.54mm_Vertical; MPN Samtec TSW-002-07-S-S
J4: USB4105-GF-A; Connector_USB_USB_C_Receptacle_GCT_USB4105-xx-A_16P_TopMnt_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; MPN USB4105-GF-A
J5: HF_INTERFACE; Connector_PinHeader_2.54mm_PinHeader_2x10_P2.54mm_Vertical; MPN Samtec TSW-010-07-D-S
J6: VHF_INTERFACE; Connector_PinHeader_2.54mm_PinHeader_2x05_P2.54mm_Vertical; MPN Samtec TSW-005-07-D-S
J7: UHF_INTERFACE; Connector_PinHeader_2.54mm_PinHeader_2x05_P2.54mm_Vertical; MPN Samtec TSW-005-07-D-S
J8: MIC_ELECTRET; Connector_PinHeader_2.54mm_PinHeader_1x02_P2.54mm_Vertical; MPN Samtec TSW-002-07-S-S
J9: SPEAKER_8_OHM; Connector_PinHeader_2.54mm_PinHeader_1x02_P2.54mm_Vertical; MPN Samtec TSW-002-07-S-S
R1, R2, R3, R4, R5, R6, R9, R20, R21: 10k; Resistor_SMD_R_0603_1608Metric; MPN CRCW0603 series; value=10k; 1%
R7, R8: 4.7k; Resistor_SMD_R_0603_1608Metric; MPN CRCW0603 series; value=4.7k; 1%
R10: 0.47; Resistor_SMD_R_0603_1608Metric; MPN CRCW0603 series; value=0.47; 1%
R11, R12: 5.1k; Resistor_SMD_R_0603_1608Metric; MPN CRCW0603 series; value=5.1k; 1%
R13, R14: 22; Resistor_SMD_R_0603_1608Metric; MPN CRCW0603 series; value=22; 1%
R15, R16, R17, R18, R19, R22, R23, R24, R25, R26, R27, R29: 100k; Resistor_SMD_R_0603_1608Metric; MPN CRCW0603 series; value=100k; 1%
R28: 2.2k; Resistor_SMD_R_0603_1608Metric; MPN CRCW0603 series; value=2.2k; 1%
R30: 10; Resistor_SMD_R_0603_1608Metric; MPN CRCW0603 series; value=10; 1%
RV1: 10k volume; Potentiometer_THT_Potentiometer_Bourns_3296W_Vertical; MPN 3296W-1-103LF
SW1, SW2, SW3, SW4, SW5: B3F-1000; Button_Switch_THT_SW_PUSH_6mm; MPN B3F-1000
U1: ESP32-S3-WROOM-1-N8; RF_Module_ESP32-S3-WROOM-1; MPN ESP32-S3-WROOM-1-N8
U2: LM1117IMP-3.3; Package_TO_SOT_SMD_SOT-223; MPN LM1117IMP-3.3
U3: USBLC6-2SC6; Package_TO_SOT_SMD_SOT-23-6; MPN USBLC6-2SC6
U4: SN74LVC1G04DBVR; Package_TO_SOT_SMD_SOT-23-5; MPN SN74LVC1G04DBVR
U5: SN74LVC1G00DBVR; Package_TO_SOT_SMD_SOT-23-5; MPN SN74LVC1G00DBVR
U6: SN74HC139D; Package_SO_SOIC-16_3.9x9.9mm_P1.27mm; MPN SN74HC139D
U7: CD74HCT4052M; Package_SO_SOIC-16_3.9x9.9mm_P1.27mm; MPN CD74HCT4052M
U8: LM386N-1; Package_DIP_DIP-8_W7.62mm; MPN LM386N-1

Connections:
+3V3: C5.1, C6.1, C7.1, C22.1, C23.1, C24.1, J2.2, J5.3, J6.10, J7.10, R1.1, R2.1, R3.2, R4.2, R5.2, R6.2, R7.2, R8.2, R9.2, R16.2, R17.2, R28.1, U1.2 (3V3), U2.2 (OUT), U2.4 (TAB), U4.5, U5.5, U6.15, U6.16
+5V: C3.1, C4.1, C19.1, C25.1, J3.1, J5.1, J6.1, J7.1, R20.1, U2.3 (IN), U7.16, U8.6
AMP_BYPASS: C18.1, U8.7
AMP_IN: RV1.2, U8.3 (IN)
AMP_OUT: C20.1, C21.1, U8.5 (OUT)
AUDIO_SELECTED: C17.1, U7.3
BOOT_N: R2.2, SW2.1, U1.27 (IO0)
BTN_BAND: R6.1, SW5.1, U1.7 (IO7)
BTN_DOWN: R4.1, SW3.1, U1.5 (IO5)
BTN_UP: R5.1, SW4.1, U1.6 (IO6)
CC1: J4.A5, R11.1
CC2: J4.B5, R12.1
CODEC_RESET_N: J5.12, U1.8 (IO15)
ESP_EN: C1.1, R1.2, SW1.1, U1.3 (EN)
FILTER_ID: C2.1, J5.17, R9.1, U1.39 (IO1)
GND: C1.2, C2.2, C3.2, C4.2, C6.2, C7.2, C8.2, C9.2, C18.2, C19.2, C22.2, C23.2, C24.2, C25.2, J1.2, J2.1, J3.2, J4.A1, J4.A12, J4.B1, J4.B12, J4.S1, J5.2, J5.4, J5.16, J5.19, J5.20, J6.2, J6.9, J7.2, J7.9, J8.2, J9.2, R10.2, R11.2, R12.2, R15.2, R18.2, R19.2, R21.2, R30.2, RV1.1, SW1.2, SW2.2, SW3.2, SW4.2, SW5.2, U1.1 (GND), U1.40 (GND), U1.41 (EP), U2.1 (GND), U3.2, U4.3, U5.3, U6.8, U6.13, U6.14, U7.6, U7.7, U7.8, U8.2, U8.4
HF_AUDIO: C10.1, J5.14
HF_AUDIO_B: C10.2, R22.1, U7.1
HF_MIC: C11.2, J5.15
HF_MIC_B: C11.1, R23.1, U7.12
HF_TX_N: J5.13, U6.4 (1Y0)
I2C_SCL: J2.3, J5.6, R8.1, U1.17 (IO9)
I2C_SDA: J2.4, J5.5, R7.1, U1.12 (IO8)
I2S_BCLK: J5.8, U1.19 (IO11)
I2S_LRCK: J5.9, U1.20 (IO12)
I2S_MCLK: J5.7, U1.18 (IO10)
I2S_RX: J5.11, U1.22 (IO14)
I2S_TX: J5.10, U1.21 (IO13)
LDO_ESR: C5.2, R10.1
LO_RESET_N: J5.18, U1.25 (IO48)
MIC_B: C16.2, R29.1, U7.13
MIC_RAW: C16.1, J8.1, R28.2
MODULE_A: R16.1, U1.32 (IO39), U6.2 (1A), U7.10
MODULE_B: R17.1, U1.33 (IO40), U6.3 (1B), U7.9
PTT_BUTTON_N: J1.1, R3.1, U1.4 (IO4), U4.2 (A)
PTT_PRESSED: U4.4 (Y), U5.1 (A)
SPEAKER: C21.2, J9.1
TX_ARM: R15.1, U1.31 (IO38), U5.2 (B)
TX_ENABLE_N: U5.4 (Y), U6.1 (1G)
UHF_AUDIO: C14.1, J7.8
UHF_AUDIO_B: C14.2, R26.1, U7.2
UHF_MIC: C15.2, J7.7
UHF_MIC_B: C15.1, R27.1, U7.15
UHF_PD: J7.6, R19.1, U1.35 (IO42)
UHF_PTT_N: J7.5, U6.6 (1Y2)
UHF_RX: J7.4, U1.11 (IO18)
UHF_TX: J7.3, U1.23 (IO21)
USB_DM: R13.2, U1.13 (IO19)
USB_DM_CONN: J4.A7, J4.B7, R13.1, U3.3, U3.4
USB_DP: R14.2, U1.14 (IO20)
USB_DP_CONN: J4.A6, J4.B6, R14.1, U3.1, U3.6
VBUS_USB: C8.1, J4.A4, J4.A9, J4.B4, J4.B9, U3.5
VHF_AUDIO: C12.1, J6.8
VHF_AUDIO_B: C12.2, R24.1, U7.5
VHF_MIC: C13.2, J6.7
VHF_MIC_B: C13.1, R25.1, U7.14
VHF_PD: J6.6, R18.1, U1.34 (IO41)
VHF_PTT_N: J6.5, U6.5 (1Y1)
VHF_RX: J6.4, U1.9 (IO16)
VHF_TX: J6.3, U1.10 (IO17)
VMID: C9.1, R20.2, R21.1, R22.2, R23.2, R24.2, R25.2, R26.2, R27.2, R29.2, U7.4, U7.11
VOL_TOP: C17.2, RV1.3
ZOBEL: C20.2, R30.1
